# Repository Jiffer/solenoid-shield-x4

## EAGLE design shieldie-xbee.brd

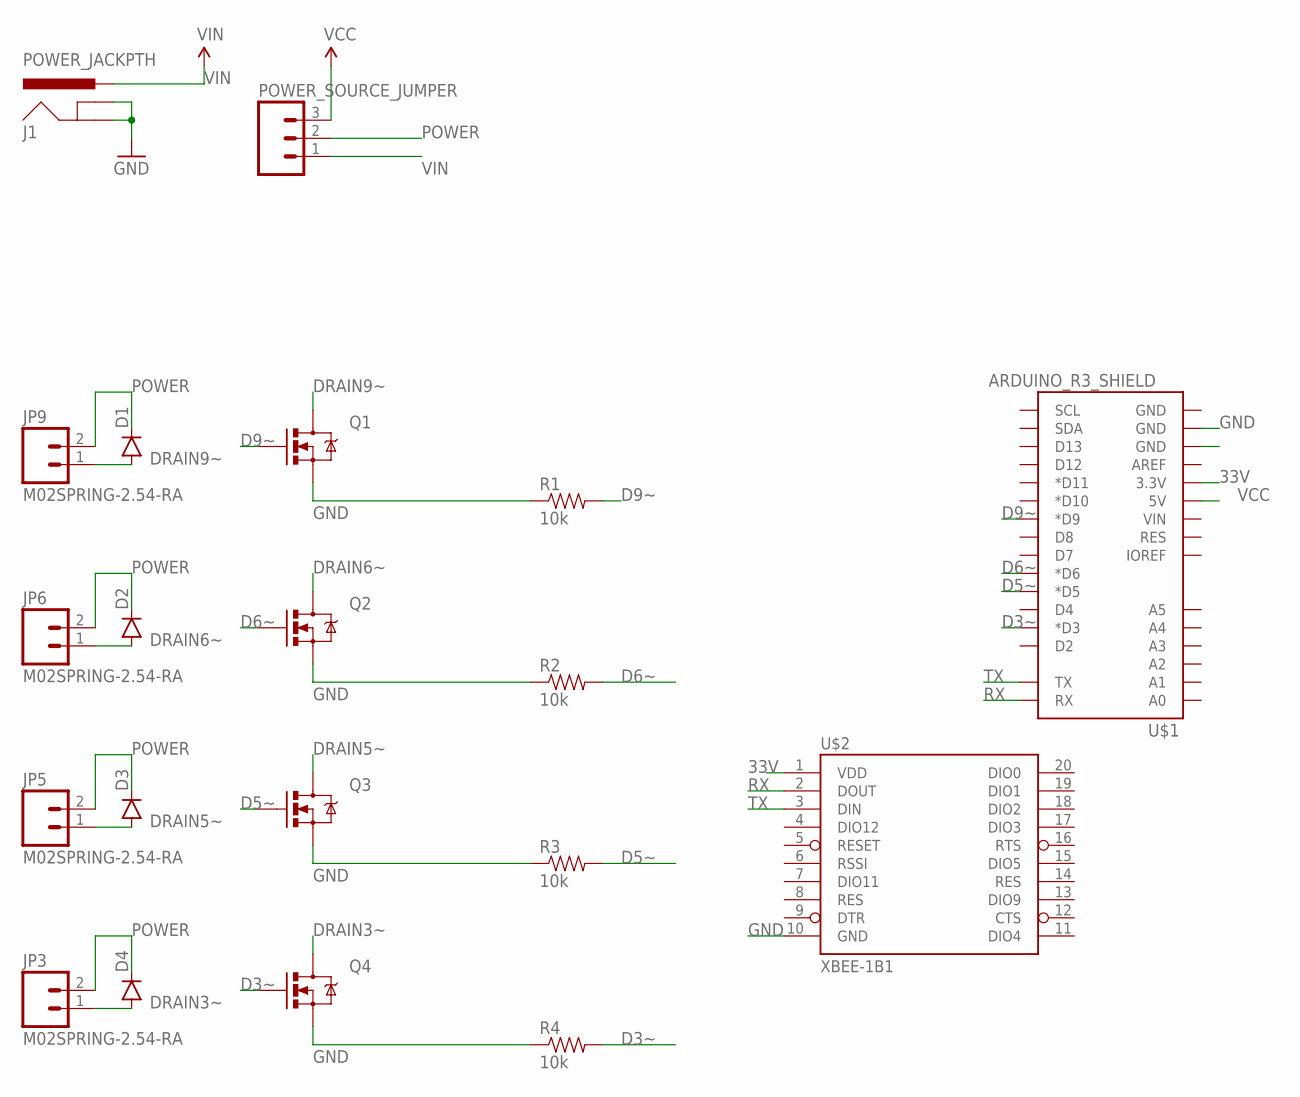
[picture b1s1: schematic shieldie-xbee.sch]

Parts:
D1, D2, D3, D4: DIODEPTH; DIODE-1N4001
J1: POWER_JACKPTH; POWER_JACK_PTH
JP3, JP5, JP6, JP9: M02SPRING-2.54-RA; SPRINGTERMINAL-2.54MM-2
POWER_SOURCE_JUMPER: M03JST-PTH-VERT; JST-3-PTH-VERT
Q1, Q2, Q3, Q4: MOSFET-NCHANNELFQP30N06L; TO220V
R1, R2, R3, R4: 10k; AXIAL-0.3
U$1: ARDUINO_R3_SHIELD; UNO_R3_SHIELD
U$2: XBEE-1B1; XBEE-1

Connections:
33V: U$1.3.3V, U$2.1 (VDD)
D3~: Q4.1 (G), R4.P$2 (2), U$1.D3 (*D3)
D5~: Q3.1 (G), R3.P$2 (2), U$1.D5 (*D5)
D6~: Q2.1 (G), R2.P$2 (2), U$1.D6 (*D6)
D9~: Q1.1 (G), R1.P$2 (2), U$1.D9 (*D9)
DRAIN3~: D4.A, JP3.1, Q4.2 (D)
DRAIN5~: D3.A, JP5.1, Q3.2 (D)
DRAIN6~: D2.A, JP6.1, Q2.2 (D)
DRAIN9~: D1.A, JP9.1, Q1.2 (D)
GND: J1.GND, J1.GNDBREAK, Q1.3 (S), Q2.3 (S), Q3.3 (S), Q4.3 (S), R1.P$1 (1), R2.P$1 (1), R3.P$1 (1), R4.P$1 (1), U$1.GND@1 (GND), U$1.GND@2 (GND), U$2.10 (GND)
POWER: D1.C, D2.C, D3.C, D4.C, JP3.2, JP5.2, JP6.2, JP9.2, POWER_SOURCE_JUMPER.2
RX: U$1.RX, U$2.2 (DOUT)
TX: U$1.TX, U$2.3 (DIN)
VCC: POWER_SOURCE_JUMPER.3, U$1.5V
VIN: J1.PWR, POWER_SOURCE_JUMPER.1

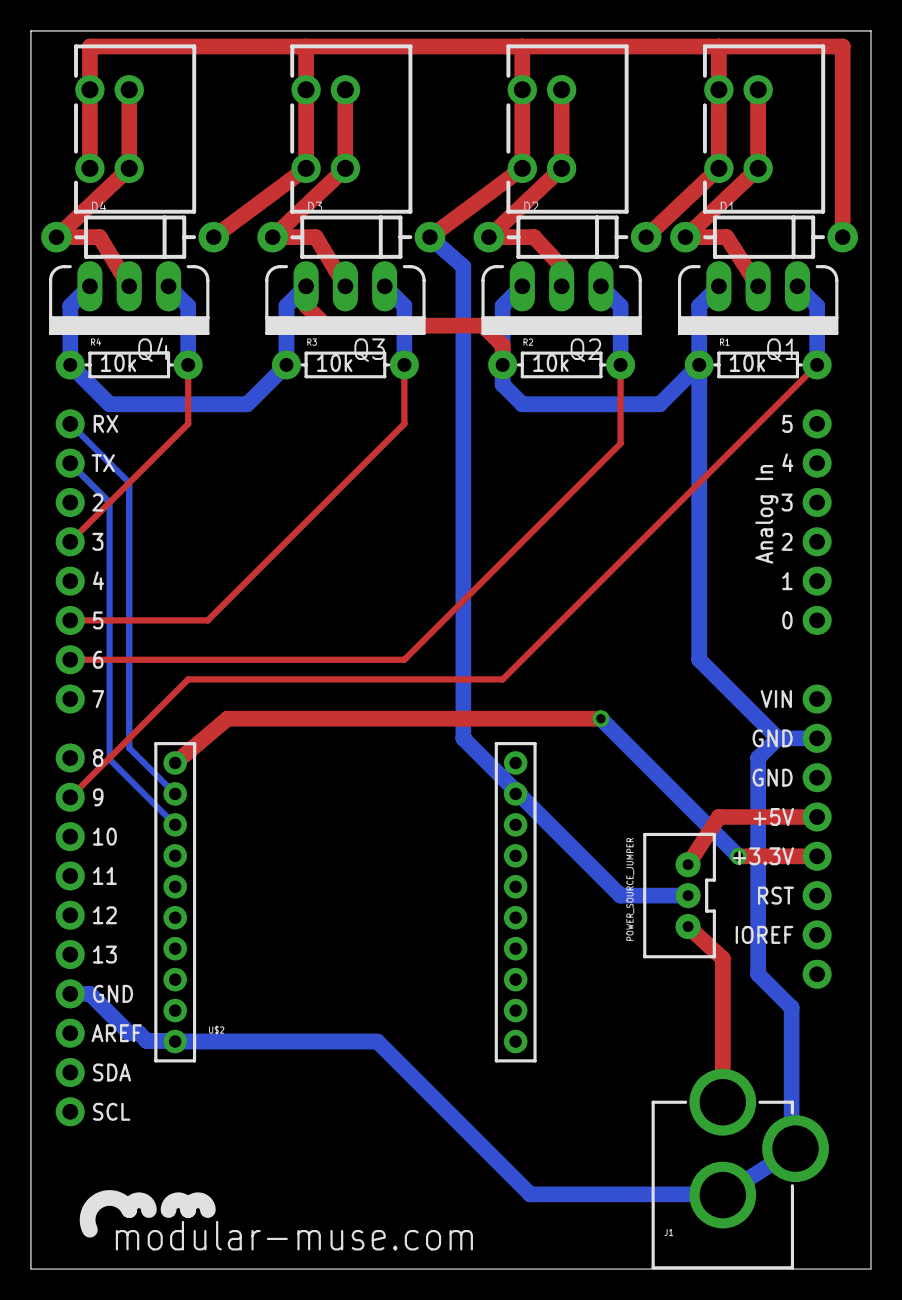
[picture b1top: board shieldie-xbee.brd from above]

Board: 2 copper layers, 54.3 x 80.0 mm, 20 parts (0 on the bottom side), 15 nets.

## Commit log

2015-02-23 added PDFs of board and schematic

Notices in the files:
parts and their libraries:
SparkFun-Connectors: Licensing: Creative Commons ShareAlike 4.0 International - https://creativecommons.org/licenses/by-sa/4.0
